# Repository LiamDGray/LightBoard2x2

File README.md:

High-power 2x2 LED board based on PicoBuck LED Driver
===================

### Repository Contents
-------------------
- Design notes.docx
- Eagle CAD source files/
- LICENSE.md
- Light bar schematic.pdf
- Mechanical_drawing_of_board_for_subs.pdf
- Photos of Chinese product/
- Quotes/
- README.md (this file)
- Requirements traceability matrix.xlsx
- Simulations _ spreadsheets/
- Specifications for board fab _ assembly/
- Test results/

### License Information
-------------------
- The hardware is released under [Creative Commons Attribution-ShareAlike 3.0 Unported (CC BY-SA 3.0)](http://creativecommons.org/licenses/by-sa/3.0/).  Please feel free to do anything you want with it; just keep this license attached.

### Additional Information
----------------------
- My starting point was the [SparkFun PicoBuck](https://github.com/sparkfun/PicoBuck) LED driver, which was a collaboration with Ethan Zonca and also licensed under CC BY-SA 3.0.
- I used Eagle CAD 7.2.0 (a version current in early 2015).
- I added thermal foldback and dimming.
- I designed this board in 2015 at the request of [Traxda, LLC](https://www.traxda.com/) in Tucson, Arizona, USA. Traxda was kind enough to accept the work product under this same license (CC BY-SA 3.0).
- This was my first LED board, my first constant-current power supply, my first use of thermal foldback, my first dimming LED driver, and my first PCB. Back in 2015, I fabricated multiple iterations of the board and did basic functional testing, but I was unable to find a subcontractor with the equipment to test for electromagnetic compatibility (EMC) or otherwise review my design. My client, Traxda, opted not to have me finish, and I moved on to other things.
- In 2023, I am thinking of adapting the design for something related to LiFi and OpenVLC.
- If you have any suggestions, please open an issue or, better yet, make a pull request!
- You're welcome to sponsor my work through [Github Sponsors](https://github.com/sponsors/LiamDGray/).

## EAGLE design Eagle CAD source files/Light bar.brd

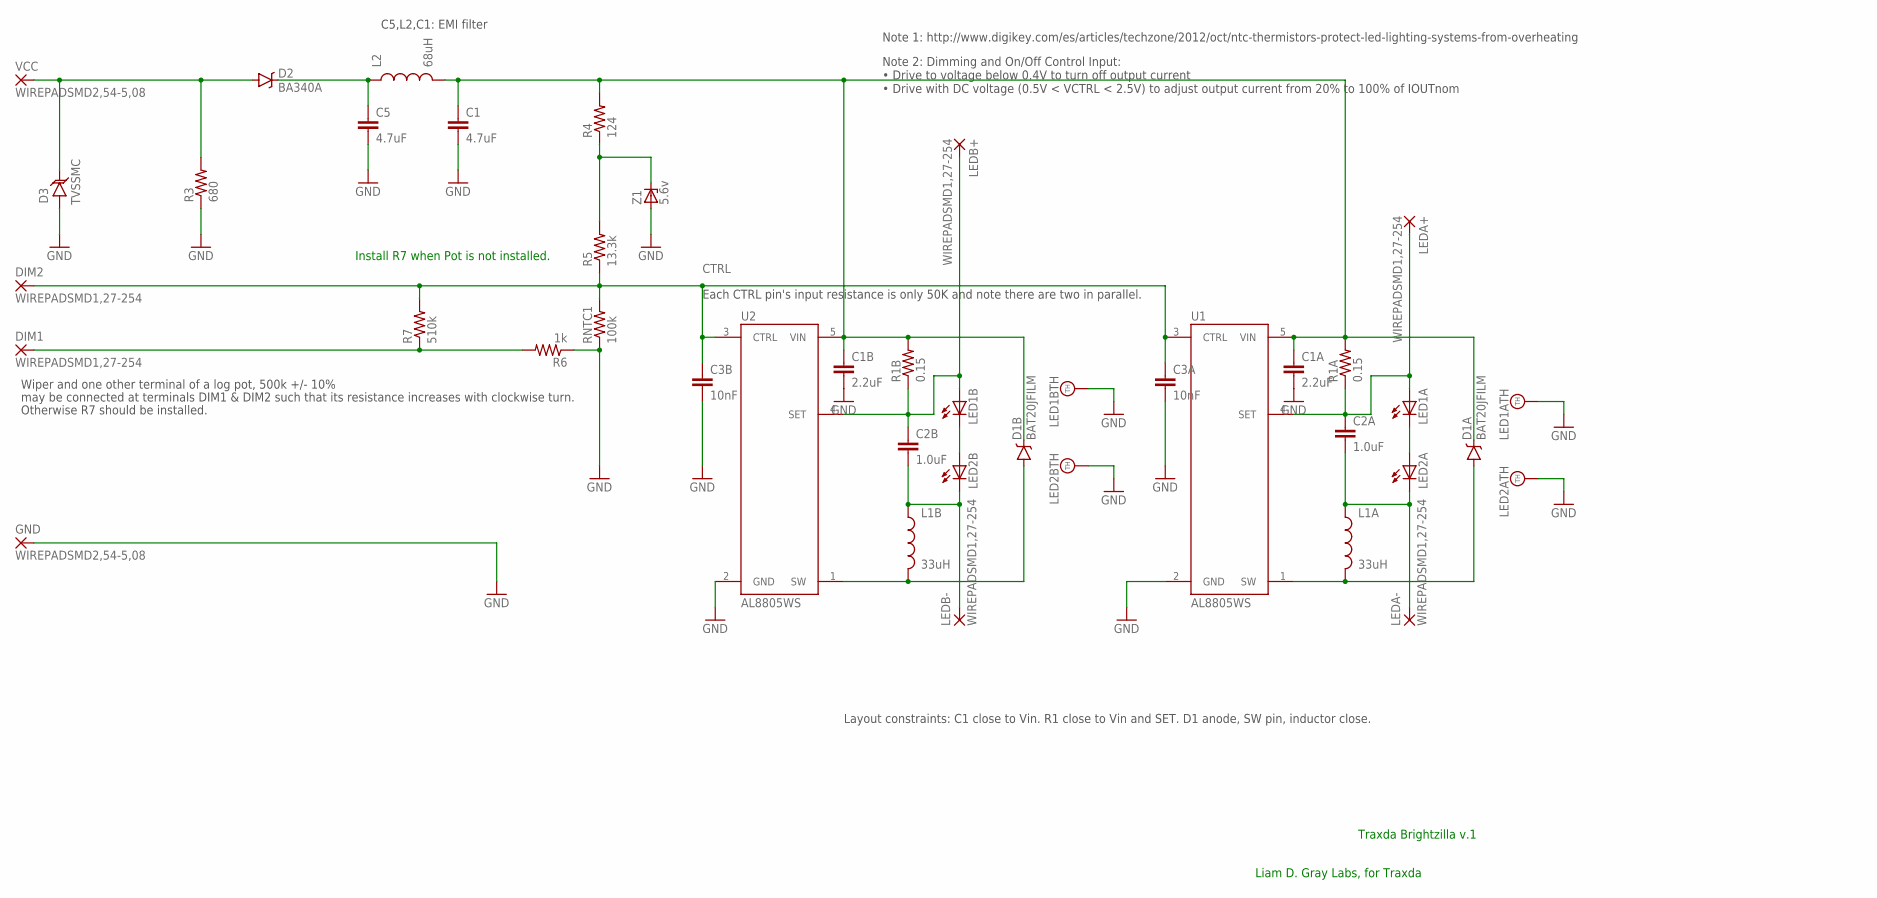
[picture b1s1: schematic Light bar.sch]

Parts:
C1, C5: 4.7uF; 1210
C1A, C1B: 2.2uF; 0805
C2A, C2B: 1.0uF; 0805
C3A, C3B: 10nF; 0603-CAP
D1A, D1B: BAT20JFILM; SOD-323
D2: BA340A; SMA-DIODE
D3: TVSSMC; SMC
DIM1, DIM2: WIREPADSMD1,27-254; SMD1,27-2,54
GND: WIREPADSMD2,54-5,08; SMD2,54-5,08
L1A, L1B: 33uH; NR6045
L2: 68uH; SRR1260
LED1A, LED1B, LED2A, LED2B: LUXEON_REBEL; LUXEON_REBEL_32MIL12MIL
LEDA+: WIREPADSMD1,27-254; SMD1,27-2,54
LEDA-: WIREPADSMD1,27-254; SMD1,27-2,54
LEDB+: WIREPADSMD1,27-254; SMD1,27-2,54
LEDB-: WIREPADSMD1,27-254; SMD1,27-2,54
R1A, R1B: 0.15; 0805
R3: 680; R2512
R4: 124; R1210
R5: 13.3k; R0805
R6: 1k; 0603-RES
R7: 510k; 0805
RNTC1: 100k; 0603-RES
U1, U2: AL8805WS; SOT23-5
VCC: WIREPADSMD2,54-5,08; SMD2,54-5,08
Z1: 5.6v; SOD80C

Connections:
CTRL: C3A.1, C3B.1, DIM2.1, R5.1, R7.2, RNTC1.2, U1.3 (CTRL), U2.3 (CTRL)
GND: C1.2, C1A.2, C1B.2, C3A.2, C3B.2, C5.2, D3.A, GND.1, LED1A.TH, LED1A.TH@1 (TH), LED1A.TH@2 (TH), LED1A.TH@3 (TH), LED1A.TH@4 (TH), LED1B.TH, LED1B.TH@1 (TH), LED1B.TH@2 (TH), LED1B.TH@3 (TH), LED1B.TH@4 (TH), LED2A.TH, LED2A.TH@1 (TH), LED2A.TH@2 (TH), LED2A.TH@3 (TH), LED2A.TH@4 (TH), LED2B.TH, LED2B.TH@1 (TH), LED2B.TH@2 (TH), LED2B.TH@3 (TH), LED2B.TH@4 (TH), R3.1, R6.1, RNTC1.1, U1.2 (GND), U2.2 (GND), Z1.A
unnamed: DIM1.1, R6.2, R7.1
unnamed: R4.1, R5.2, Z1.C
unnamed: LED1B.C, LED1B.C@1 (C), LED2B.A, LED2B.A@1 (A)
unnamed: LED1A.C, LED1A.C@1 (C), LED2A.A, LED2A.A@1 (A)
unnamed: C5.1, D2.C, L2.1
unnamed: C2A.2, L1A.1, LED2A.C, LED2A.C@1 (C), LEDA-.1
unnamed: C2B.2, L1B.1, LED2B.C, LED2B.C@1 (C), LEDB-.1
SET1: C2A.1, LED1A.A, LED1A.A@1 (A), LEDA+.1, R1A.1, U1.4 (SET)
SET2: C2B.1, LED1B.A, LED1B.A@1 (A), LEDB+.1, R1B.1, U2.4 (SET)
SW1: D1A.A, L1A.2, U1.1 (SW)
SW2: D1B.A, L1B.2, U2.1 (SW)
VCC: D2.A, D3.C, R3.2, VCC.1
VIN: C1.1, C1A.1, C1B.1, D1A.C, D1B.C, L2.2, R1A.2, R1B.2, R4.2, U1.5 (VIN), U2.5 (VIN)

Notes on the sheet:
Liam D. Gray Labs, for Traxda
Traxda Brightzilla v.1
Note 1: http://www.digikey.com/es/articles/techzone/2012/oct/ntc-thermistors-protect-led-lighting-systems-from-overheating
Note 2: Dimming and On/Off Control Input: • Drive to voltage below 0.4V to turn off output current • Drive with DC voltage (0.5V < VCTRL < 2.5V) to adjust output current from 20% to 100% of IOUTnom
Each CTRL pin's input resistance is only 50K and note there are two in parallel.
Wiper and one other terminal of a log pot, 500k +/- 10%
Layout constraints: C1 close to Vin. R1 close to Vin and SET. D1 anode, SW pin, inductor close.
C5,L2,C1: EMI filter
may be connected at terminals DIM1 & DIM2 such that its resistance increases with clockwise turn.
Install R7 when Pot is not installed.
Otherwise R7 should be installed.

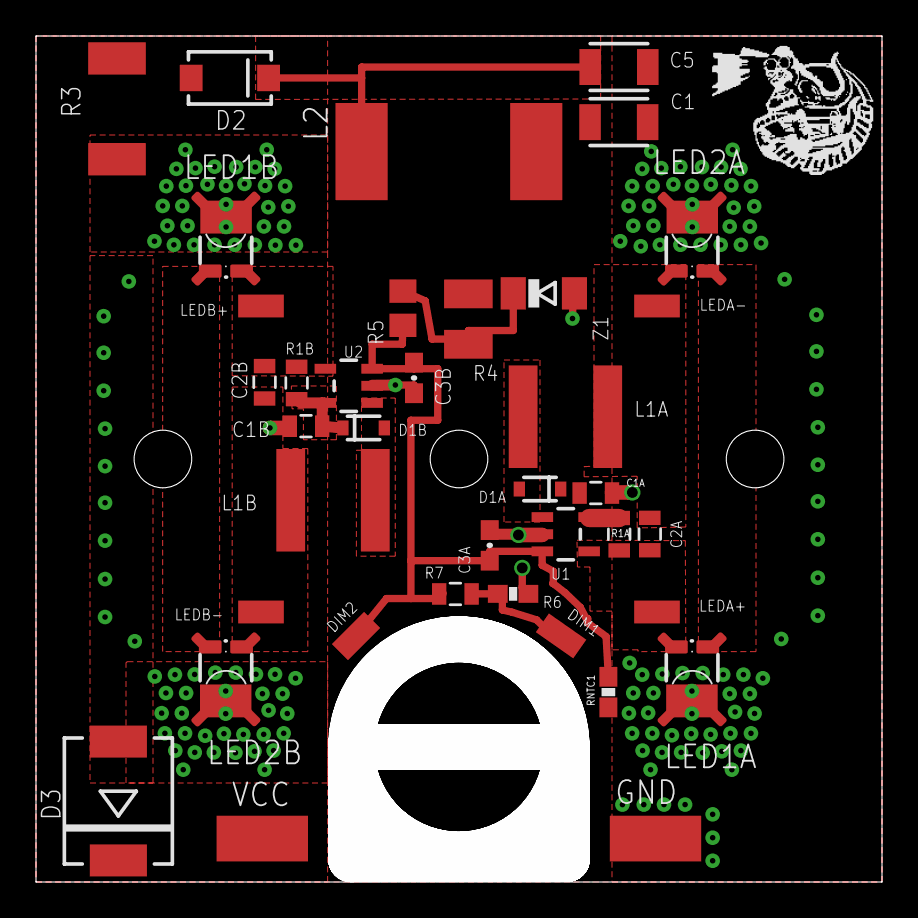
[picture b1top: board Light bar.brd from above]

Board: 2 copper layers, 47.0 x 47.0 mm, 39 parts (0 on the bottom side), 15 nets.

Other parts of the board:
DRILEGEND: DRILEGEND

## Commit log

2023-06-12 Initial commit of the 2015 design
2023-06-12 Added license
2023-06-12 Formatted LICENSE as Markdown
2023-06-12 Removed old versions

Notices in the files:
parts and their libraries:
SparkFun-Capacitors: Licensing: Creative Commons ShareAlike 4.0 International - https://creativecommons.org/licenses/by-sa/4.0
